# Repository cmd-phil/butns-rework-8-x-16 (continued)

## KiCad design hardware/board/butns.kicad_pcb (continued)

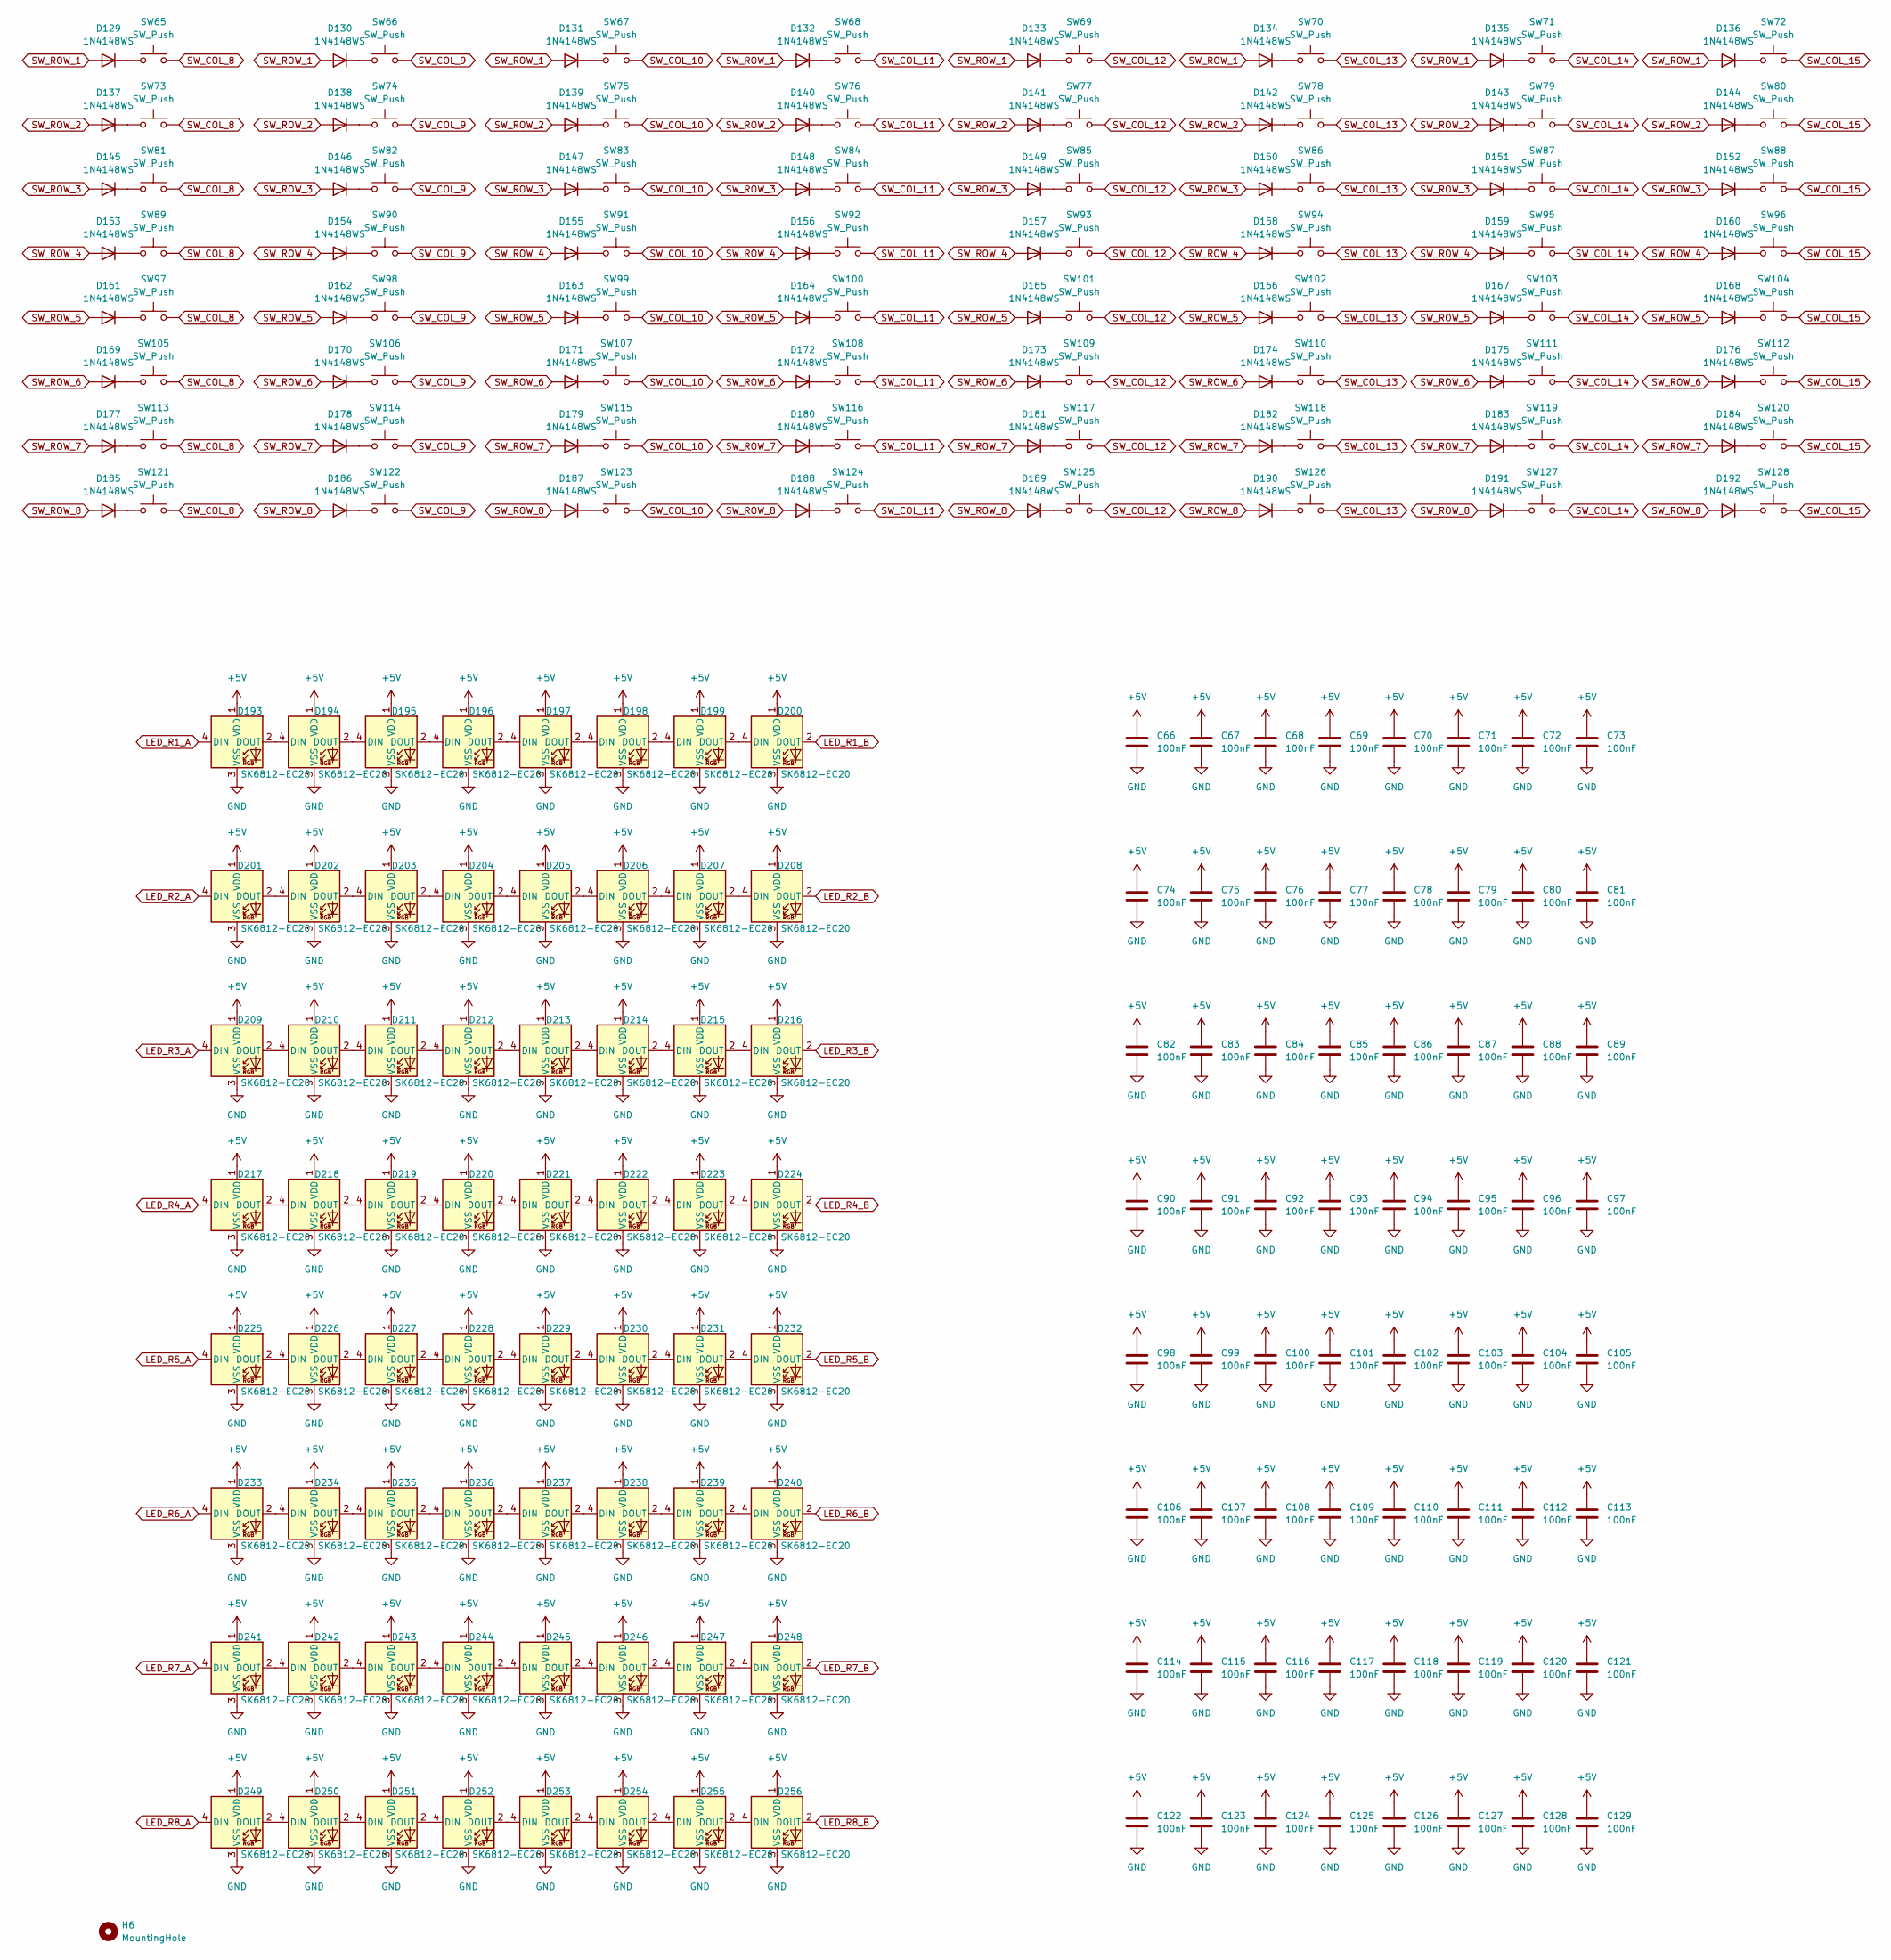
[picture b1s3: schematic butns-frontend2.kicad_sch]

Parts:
C66, C67, C68, C69, C70, C71, C72, C73, C74, C75, C76, C77, C78, C79, C80, C81, C82, C83, C84, C85, C86, C87, C88, C89, C90, C91, C92, C93, C94, C95, C96, C97, C98, C99, C100, C101, C102, C103, C104, C105, C106, C107, C108, C109, C110, C111, C112, C113, C114, C115, C116, C117, C118, C119, C120, C121, C122, C123, C124, C125, C126, C127, C128, C129: 100nF; C_0603_1608Metric; LCSC C14663
D129, D130, D131, D132, D133, D134, D135, D136, D137, D138, D139, D140, D141, D142, D143, D144, D145, D146, D147, D148, D149, D150, D151, D152, D153, D154, D155, D156, D157, D158, D159, D160, D161, D162, D163, D164, D165, D166, D167, D168, D169, D170, D171, D172, D173, D174, D175, D176, D177, D178, D179, D180, D181, D182, D183, D184, D185, D186, D187, D188, D189, D190, D191, D192: 1N4148WS; D_SOD-323; LCSC C2128
D193, D194, D195, D196, D197, D198, D199, D200, D201, D202, D203, D204, D205, D206, D207, D208, D209, D210, D211, D212, D213, D214, D215, D216, D217, D218, D219, D220, D221, D222, D223, D224, D225, D226, D227, D228, D229, D230, D231, D232, D233, D234, D235, D236, D237, D238, D239, D240, D241, D242, D243, D244, D245, D246, D247, D248, D249, D250, D251, D252, D253, D254, D255, D256: SK6812-EC20; LCSC C2909058
H6: MountingHole; MountingHole_2.7mm_M2.5
SW65, SW66, SW67, SW68, SW69, SW70, SW71, SW72, SW73, SW74, SW75, SW76, SW77, SW78, SW79, SW80, SW81, SW82, SW83, SW84, SW85, SW86, SW87, SW88, SW89, SW90, SW91, SW92, SW93, SW94, SW95, SW96, SW97, SW98, SW99, SW100, SW101, SW102, SW103, SW104, SW105, SW106, SW107, SW108, SW109, SW110, SW111, SW112, SW113, SW114, SW115, SW116, SW117, SW118, SW119, SW120, SW121, SW122, SW123, SW124, SW125, SW126, SW127, SW128: SW_Push; SW_Push_1P1T_XKB_TS-1187A; LCSC C318884

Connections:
+5V: C66.1, C67.1, C68.1, C69.1, C70.1, C71.1, C72.1, C73.1, C74.1, C75.1, C76.1, C77.1, C78.1, C79.1, C80.1, C81.1, C82.1, C83.1, C84.1, C85.1, C86.1, C87.1, C88.1, C89.1, C90.1, C91.1, C92.1, C93.1, C94.1, C95.1, C96.1, C97.1, C98.1, C99.1, C100.1, C101.1, C102.1, C103.1, C104.1, C105.1, C106.1, C107.1, C108.1, C109.1, C110.1, C111.1, C112.1, C113.1, C114.1, C115.1, C116.1, C117.1, C118.1, C119.1, C120.1, C121.1, C122.1, C123.1, C124.1, C125.1, C126.1, C127.1, C128.1, C129.1, D193.1 (VDD), D194.1 (VDD), D195.1 (VDD), D196.1 (VDD), D197.1 (VDD), D198.1 (VDD), D199.1 (VDD), D200.1 (VDD), D201.1 (VDD), D202.1 (VDD), D203.1 (VDD), D204.1 (VDD), D205.1 (VDD), D206.1 (VDD), D207.1 (VDD), D208.1 (VDD), D209.1 (VDD), D210.1 (VDD), D211.1 (VDD), D212.1 (VDD), D213.1 (VDD), D214.1 (VDD), D215.1 (VDD), D216.1 (VDD), D217.1 (VDD), D218.1 (VDD), D219.1 (VDD), D220.1 (VDD), D221.1 (VDD), D222.1 (VDD), D223.1 (VDD), D224.1 (VDD), D225.1 (VDD), D226.1 (VDD), D227.1 (VDD), D228.1 (VDD), D229.1 (VDD), D230.1 (VDD), D231.1 (VDD), D232.1 (VDD), D233.1 (VDD), D234.1 (VDD), D235.1 (VDD), D236.1 (VDD), D237.1 (VDD), D238.1 (VDD), D239.1 (VDD), D240.1 (VDD), D241.1 (VDD), D242.1 (VDD), D243.1 (VDD), D244.1 (VDD), D245.1 (VDD), D246.1 (VDD), D247.1 (VDD), D248.1 (VDD), D249.1 (VDD), D250.1 (VDD), D251.1 (VDD), D252.1 (VDD), D253.1 (VDD), D254.1 (VDD), D255.1 (VDD), D256.1 (VDD); also elsewhere on the board
GND: C66.2, C67.2, C68.2, C69.2, C70.2, C71.2, C72.2, C73.2, C74.2, C75.2, C76.2, C77.2, C78.2, C79.2, C80.2, C81.2, C82.2, C83.2, C84.2, C85.2, C86.2, C87.2, C88.2, C89.2, C90.2, C91.2, C92.2, C93.2, C94.2, C95.2, C96.2, C97.2, C98.2, C99.2, C100.2, C101.2, C102.2, C103.2, C104.2, C105.2, C106.2, C107.2, C108.2, C109.2, C110.2, C111.2, C112.2, C113.2, C114.2, C115.2, C116.2, C117.2, C118.2, C119.2, C120.2, C121.2, C122.2, C123.2, C124.2, C125.2, C126.2, C127.2, C128.2, C129.2, D193.3 (VSS), D194.3 (VSS), D195.3 (VSS), D196.3 (VSS), D197.3 (VSS), D198.3 (VSS), D199.3 (VSS), D200.3 (VSS), D201.3 (VSS), D202.3 (VSS), D203.3 (VSS), D204.3 (VSS), D205.3 (VSS), D206.3 (VSS), D207.3 (VSS), D208.3 (VSS), D209.3 (VSS), D210.3 (VSS), D211.3 (VSS), D212.3 (VSS), D213.3 (VSS), D214.3 (VSS), D215.3 (VSS), D216.3 (VSS), D217.3 (VSS), D218.3 (VSS), D219.3 (VSS), D220.3 (VSS), D221.3 (VSS), D222.3 (VSS), D223.3 (VSS), D224.3 (VSS), D225.3 (VSS), D226.3 (VSS), D227.3 (VSS), D228.3 (VSS), D229.3 (VSS), D230.3 (VSS), D231.3 (VSS), D232.3 (VSS), D233.3 (VSS), D234.3 (VSS), D235.3 (VSS), D236.3 (VSS), D237.3 (VSS), D238.3 (VSS), D239.3 (VSS), D240.3 (VSS), D241.3 (VSS), D242.3 (VSS), D243.3 (VSS), D244.3 (VSS), D245.3 (VSS), D246.3 (VSS), D247.3 (VSS), D248.3 (VSS), D249.3 (VSS), D250.3 (VSS), D251.3 (VSS), D252.3 (VSS), D253.3 (VSS), D254.3 (VSS), D255.3 (VSS), D256.3 (VSS); also elsewhere on the board
LED_R1_A: D193.4 (DIN); also elsewhere on the board
LED_R1_B: D200.2 (DOUT); also elsewhere on the board
LED_R2_A: D201.4 (DIN); also elsewhere on the board
LED_R2_B: D208.2 (DOUT); also elsewhere on the board
LED_R3_A: D209.4 (DIN); also elsewhere on the board
LED_R3_B: D216.2 (DOUT); also elsewhere on the board
LED_R4_A: D217.4 (DIN); also elsewhere on the board
LED_R4_B: D224.2 (DOUT); also elsewhere on the board
LED_R5_A: D225.4 (DIN); also elsewhere on the board
LED_R5_B: D232.2 (DOUT); also elsewhere on the board
LED_R6_A: D233.4 (DIN); also elsewhere on the board
LED_R6_B: D240.2 (DOUT); also elsewhere on the board
LED_R7_A: D241.4 (DIN); also elsewhere on the board
LED_R7_B: D248.2 (DOUT); also elsewhere on the board
LED_R8_A: D249.4 (DIN); also elsewhere on the board
LED_R8_B: D256.2 (DOUT); also elsewhere on the board
unnamed: D129.1 (K), SW65.1
unnamed: D130.1 (K), SW66.1
unnamed: D131.1 (K), SW67.1
unnamed: D132.1 (K), SW68.1
unnamed: D133.1 (K), SW69.1
unnamed: D134.1 (K), SW70.1
unnamed: D135.1 (K), SW71.1
unnamed: D136.1 (K), SW72.1
unnamed: D137.1 (K), SW73.1
unnamed: D138.1 (K), SW74.1
unnamed: D139.1 (K), SW75.1
unnamed: D140.1 (K), SW76.1
unnamed: D141.1 (K), SW77.1
unnamed: D142.1 (K), SW78.1
unnamed: D143.1 (K), SW79.1
unnamed: D144.1 (K), SW80.1
unnamed: D145.1 (K), SW81.1
unnamed: D146.1 (K), SW82.1
unnamed: D147.1 (K), SW83.1
unnamed: D148.1 (K), SW84.1
unnamed: D149.1 (K), SW85.1
unnamed: D150.1 (K), SW86.1
unnamed: D151.1 (K), SW87.1
unnamed: D152.1 (K), SW88.1
unnamed: D153.1 (K), SW89.1
unnamed: D154.1 (K), SW90.1
unnamed: D155.1 (K), SW91.1
unnamed: D156.1 (K), SW92.1
unnamed: D157.1 (K), SW93.1
unnamed: D158.1 (K), SW94.1
unnamed: D159.1 (K), SW95.1
unnamed: D160.1 (K), SW96.1
unnamed: D161.1 (K), SW97.1
unnamed: D162.1 (K), SW98.1
unnamed: D163.1 (K), SW99.1
unnamed: D164.1 (K), SW100.1
unnamed: D165.1 (K), SW101.1
unnamed: D166.1 (K), SW102.1
unnamed: D167.1 (K), SW103.1
unnamed: D168.1 (K), SW104.1
unnamed: D169.1 (K), SW105.1
unnamed: D170.1 (K), SW106.1
unnamed: D171.1 (K), SW107.1
unnamed: D172.1 (K), SW108.1
unnamed: D173.1 (K), SW109.1
unnamed: D174.1 (K), SW110.1
unnamed: D175.1 (K), SW111.1
unnamed: D176.1 (K), SW112.1
unnamed: D177.1 (K), SW113.1
unnamed: D178.1 (K), SW114.1
unnamed: D179.1 (K), SW115.1
unnamed: D180.1 (K), SW116.1
unnamed: D181.1 (K), SW117.1
unnamed: D182.1 (K), SW118.1
unnamed: D183.1 (K), SW119.1
unnamed: D184.1 (K), SW120.1
unnamed: D185.1 (K), SW121.1
unnamed: D186.1 (K), SW122.1
unnamed: D187.1 (K), SW123.1
unnamed: D188.1 (K), SW124.1
unnamed: D189.1 (K), SW125.1
unnamed: D190.1 (K), SW126.1
unnamed: D191.1 (K), SW127.1
unnamed: D192.1 (K), SW128.1
unnamed: D193.2 (DOUT), D194.4 (DIN)
unnamed: D194.2 (DOUT), D195.4 (DIN)
unnamed: D195.2 (DOUT), D196.4 (DIN)
unnamed: D196.2 (DOUT), D197.4 (DIN)
unnamed: D197.2 (DOUT), D198.4 (DIN)
unnamed: D198.2 (DOUT), D199.4 (DIN)
unnamed: D199.2 (DOUT), D200.4 (DIN)
unnamed: D201.2 (DOUT), D202.4 (DIN)
unnamed: D202.2 (DOUT), D203.4 (DIN)
unnamed: D203.2 (DOUT), D204.4 (DIN)
unnamed: D204.2 (DOUT), D205.4 (DIN)
unnamed: D205.2 (DOUT), D206.4 (DIN)
unnamed: D206.2 (DOUT), D207.4 (DIN)
unnamed: D207.2 (DOUT), D208.4 (DIN)
unnamed: D209.2 (DOUT), D210.4 (DIN)
unnamed: D210.2 (DOUT), D211.4 (DIN)
unnamed: D211.2 (DOUT), D212.4 (DIN)
unnamed: D212.2 (DOUT), D213.4 (DIN)
unnamed: D213.2 (DOUT), D214.4 (DIN)
unnamed: D214.2 (DOUT), D215.4 (DIN)
unnamed: D215.2 (DOUT), D216.4 (DIN)
unnamed: D217.2 (DOUT), D218.4 (DIN)
unnamed: D218.2 (DOUT), D219.4 (DIN)
unnamed: D219.2 (DOUT), D220.4 (DIN)
unnamed: D220.2 (DOUT), D221.4 (DIN)
unnamed: D221.2 (DOUT), D222.4 (DIN)
unnamed: D222.2 (DOUT), D223.4 (DIN)
unnamed: D223.2 (DOUT), D224.4 (DIN)
unnamed: D225.2 (DOUT), D226.4 (DIN)
unnamed: D226.2 (DOUT), D227.4 (DIN)
unnamed: D227.2 (DOUT), D228.4 (DIN)
unnamed: D228.2 (DOUT), D229.4 (DIN)
unnamed: D229.2 (DOUT), D230.4 (DIN)
unnamed: D230.2 (DOUT), D231.4 (DIN)
unnamed: D231.2 (DOUT), D232.4 (DIN)
unnamed: D233.2 (DOUT), D234.4 (DIN)
unnamed: D234.2 (DOUT), D235.4 (DIN)
unnamed: D235.2 (DOUT), D236.4 (DIN)
unnamed: D236.2 (DOUT), D237.4 (DIN)
unnamed: D237.2 (DOUT), D238.4 (DIN)
unnamed: D238.2 (DOUT), D239.4 (DIN)
unnamed: D239.2 (DOUT), D240.4 (DIN)
unnamed: D241.2 (DOUT), D242.4 (DIN)
unnamed: D242.2 (DOUT), D243.4 (DIN)
unnamed: D243.2 (DOUT), D244.4 (DIN)
unnamed: D244.2 (DOUT), D245.4 (DIN)
unnamed: D245.2 (DOUT), D246.4 (DIN)
unnamed: D246.2 (DOUT), D247.4 (DIN)
unnamed: D247.2 (DOUT), D248.4 (DIN)
unnamed: D249.2 (DOUT), D250.4 (DIN)
unnamed: D250.2 (DOUT), D251.4 (DIN)
unnamed: D251.2 (DOUT), D252.4 (DIN)
unnamed: D252.2 (DOUT), D253.4 (DIN)
unnamed: D253.2 (DOUT), D254.4 (DIN)
unnamed: D254.2 (DOUT), D255.4 (DIN)
unnamed: D255.2 (DOUT), D256.4 (DIN)
SW_COL_8: SW65.2, SW73.2, SW81.2, SW89.2, SW97.2, SW105.2, SW113.2, SW121.2; also elsewhere on the board
SW_COL_9: SW66.2, SW74.2, SW82.2, SW90.2, SW98.2, SW106.2, SW114.2, SW122.2; also elsewhere on the board
SW_COL_10: SW67.2, SW75.2, SW83.2, SW91.2, SW99.2, SW107.2, SW115.2, SW123.2; also elsewhere on the board
SW_COL_11: SW68.2, SW76.2, SW84.2, SW92.2, SW100.2, SW108.2, SW116.2, SW124.2; also elsewhere on the board
SW_COL_12: SW69.2, SW77.2, SW85.2, SW93.2, SW101.2, SW109.2, SW117.2, SW125.2; also elsewhere on the board
SW_COL_13: SW70.2, SW78.2, SW86.2, SW94.2, SW102.2, SW110.2, SW118.2, SW126.2; also elsewhere on the board
SW_COL_14: SW71.2, SW79.2, SW87.2, SW95.2, SW103.2, SW111.2, SW119.2, SW127.2; also elsewhere on the board
SW_COL_15: SW72.2, SW80.2, SW88.2, SW96.2, SW104.2, SW112.2, SW120.2, SW128.2; also elsewhere on the board
SW_ROW_1: D129.2 (A), D130.2 (A), D131.2 (A), D132.2 (A), D133.2 (A), D134.2 (A), D135.2 (A), D136.2 (A); also elsewhere on the board
SW_ROW_2: D137.2 (A), D138.2 (A), D139.2 (A), D140.2 (A), D141.2 (A), D142.2 (A), D143.2 (A), D144.2 (A); also elsewhere on the board
SW_ROW_3: D145.2 (A), D146.2 (A), D147.2 (A), D148.2 (A), D149.2 (A), D150.2 (A), D151.2 (A), D152.2 (A); also elsewhere on the board
SW_ROW_4: D153.2 (A), D154.2 (A), D155.2 (A), D156.2 (A), D157.2 (A), D158.2 (A), D159.2 (A), D160.2 (A); also elsewhere on the board
SW_ROW_5: D161.2 (A), D162.2 (A), D163.2 (A), D164.2 (A), D165.2 (A), D166.2 (A), D167.2 (A), D168.2 (A); also elsewhere on the board
SW_ROW_6: D169.2 (A), D170.2 (A), D171.2 (A), D172.2 (A), D173.2 (A), D174.2 (A), D175.2 (A), D176.2 (A); also elsewhere on the board
SW_ROW_7: D177.2 (A), D178.2 (A), D179.2 (A), D180.2 (A), D181.2 (A), D182.2 (A), D183.2 (A), D184.2 (A); also elsewhere on the board
SW_ROW_8: D185.2 (A), D186.2 (A), D187.2 (A), D188.2 (A), D189.2 (A), D190.2 (A), D191.2 (A), D192.2 (A); also elsewhere on the board

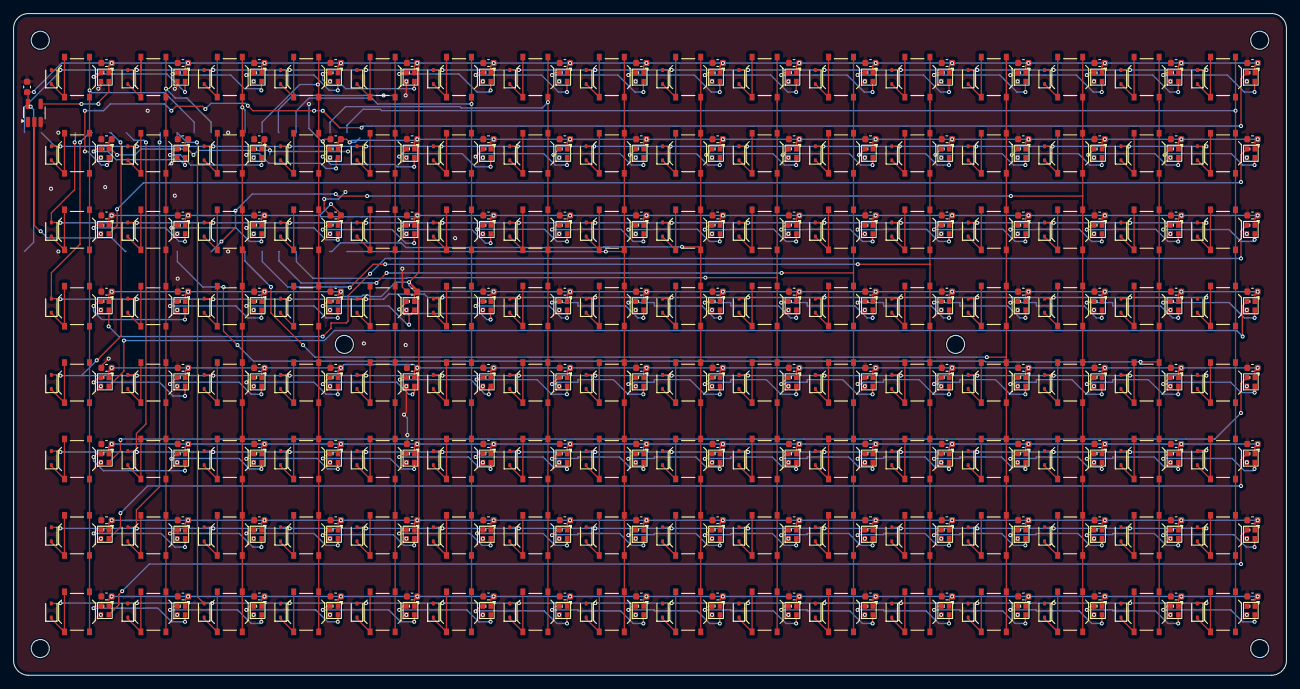
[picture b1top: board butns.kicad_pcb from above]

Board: 2 copper layers, 190.4 x 99.0 mm, 521 parts (1 on the bottom side), 283 nets.

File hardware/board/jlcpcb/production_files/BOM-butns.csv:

Comment,Designator,Footprint,LCSC,Quantity
100nF,"C1,C10,C100,C101,C102,C103,C104,C105,C106,C107,C108,C109,C11,C110,C111,C112,C113,C114,C115,C116,C117,C118,C119,C12,C120,C121,C122,C123,C124,C125,C126,C127,C128,C129,C13,C14,C15,C16,C17,C18,C19,C2,C20,C21,C22,C23,C24,C25,C26,C27,C28,C29,C3,C30,C31,C32,C33,C34,C35,C36,C37,C38,C39,C4,C40,C41,C42,C43,C44,C45,C46,C47,C48,C49,C5,C50,C51,C52,C53,C54,C55,C56,C57,C58,C59,C6,C60,C61,C62,C63,C64,C65,C66,C67,C68,C69,C7,C70,C71,C72,C73,C74,C75,C76,C77,C78,C79,C8,C80,C81,C82,C83,C84,C85,C86,C87,C88,C89,C9,C90,C91,C92,C93,C94,C95,C96,C97,C98,C99",C_0603_1608Metric,C14663,129
1N4148WS,"D10,D11,D12,D129,D13,D130,D131,D132,D133,D134,D135,D136,D137,D138,D139,D14,D140,D141,D142,D143,D144,D145,D146,D147,D148,D149,D15,D150,D151,D152,D153,D154,D155,D156,D157,D158,D159,D16,D160,D161,D162,D163,D164,D165,D166,D167,D168,D169,D17,D170,D171,D172,D173,D174,D175,D176,D177,D178,D179,D18,D180,D181,D182,D183,D184,D185,D186,D187,D188,D189,D19,D190,D191,D192,D2,D20,D21,D22,D23,D24,D25,D26,D27,D28,D29,D3,D30,D31,D32,D33,D34,D35,D36,D37,D38,D39,D4,D40,D41,D42,D43,D44,D45,D46,D47,D48,D49,D5,D50,D51,D52,D53,D54,D55,D56,D57,D58,D59,D6,D60,D61,D62,D63,D64,D65,D7,D8,D9",D_SOD-323,C2128,128
SK6812-EC20,"D1,D100,D101,D102,D103,D104,D105,D106,D107,D108,D109,D110,D111,D112,D113,D114,D115,D116,D117,D118,D119,D120,D121,D122,D123,D124,D125,D126,D127,D128,D193,D194,D195,D196,D197,D198,D199,D200,D201,D202,D203,D204,D205,D206,D207,D208,D209,D210,D211,D212,D213,D214,D215,D216,D217,D218,D219,D220,D221,D222,D223,D224,D225,D226,D227,D228,D229,D230,D231,D232,D233,D234,D235,D236,D237,D238,D239,D240,D241,D242,D243,D244,D245,D246,D247,D248,D249,D250,D251,D252,D253,D254,D255,D256,D66,D67,D68,D69,D70,D71,D72,D73,D74,D75,D76,D77,D78,D79,D80,D81,D82,D83,D84,D85,D86,D87,D88,D89,D90,D91,D92,D93,D94,D95,D96,D97,D98,D99",SK6812-EC20,C2909058,128
SW_Push,"SW1,SW10,SW100,SW101,SW102,SW103,SW104,SW105,SW106,SW107,SW108,SW109,SW11,SW110,SW111,SW112,SW113,SW114,SW115,SW116,SW117,SW118,SW119,SW12,SW120,SW121,SW122,SW123,SW124,SW125,SW126,SW127,SW128,SW13,SW14,SW15,SW16,SW17,SW18,SW19,SW2,SW20,SW21,SW22,SW23,SW24,SW25,SW26,SW27,SW28,SW29,SW3,SW30,SW31,SW32,SW33,SW34,SW35,SW36,SW37,SW38,SW39,SW4,SW40,SW41,SW42,SW43,SW44,SW45,SW46,SW47,SW48,SW49,SW5,SW50,SW51,SW52,SW53,SW54,SW55,SW56,SW57,SW58,SW59,SW6,SW60,SW61,SW62,SW63,SW64,SW65,SW66,SW67,SW68,SW69,SW7,SW70,SW71,SW72,SW73,SW74,SW75,SW76,SW77,SW78,SW79,SW8,SW80,SW81,SW82,SW83,SW84,SW85,SW86,SW87,SW88,SW89,SW9,SW90,SW91,SW92,SW93,SW94,SW95,SW96,SW97,SW98,SW99",SW_Push_1P1T_XKB_TS-1187A,C318884,128
74LVC1G17,U2,SOT-23-5_HandSoldering,C7836,1
Pico,U1,RPi_Pico_SMD_TH,,1

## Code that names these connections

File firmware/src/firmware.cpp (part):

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#define COL_SETTLE_US 5
#define COL_RELEASE_US 20

// SW_ROW_1..8 -> GPIO0..7
const uint8_t ROW_PINS[NUM_ROWS] = {0, 1, 2, 3, 4, 5, 6, 7};
// SW_COL_1..16, physical order left to right.
// Columns 1-7: GPIO8-14, columns 8-15: GPIO16-22 and GPIO26, column 16: GPIO15.
const uint8_t COL_PINS[NUM_COLS] = {8, 9, 10, 11, 12, 13, 14, 16, 17, 18, 19, 20, 21, 22, 26, 15};
const uint8_t gammaTable[16] = { 0,  2,  3,  6,  11, 18, 25, 32, 41, 59, 70, 80, 92, 103, 115, 127};
const uint8_t gammaAdj = 2;
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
